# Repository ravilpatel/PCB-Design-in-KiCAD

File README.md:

# PCB Design

**Software:** KiCAD 9.0

## Table of Content

- [STM32 - UART, I2C and SWD (From Tutorial)](#stm32---uart-i2c-and-swd-from-tutorial)
- [Motion Detector using NE555 Timer IC](#motion-detector-using-ne555-timer-ic)

---

## STM32 - UART, I2C and SWD (From Tutorial)

Compact 2-layer STM32-based PCB

[Tutorial Video Link- Phill's Lab YT](https://www.youtube.com/watch?v=aVUqaB0IMh4&pp=ygULS0lDQUQgU3RtMzI%3D)

<div align="center">

</div>

### Design specifications

* **Microcontroller (MCU):** STM32F103C8T6
* **Layers:** 2 (Top / Bottom)
* **Board dimensions:** 41 mm × 28.8 mm
* **Substrate:** FR4, 1.6 mm thickness
* **Files included:** KiCAD project files, schematic, PCB layout, Gerber export instructions, BOM
* **Protocols supported:** UART, I2C, SWD

**[Project Repo](/STM32-I2C_UART_SWD)**

---

## Motion Detector using NE555 Timer IC

2-Layer NE555 Timer IC with IR Sensor 

<div align="center">

</div>

### Design specifications

* **Integrated Circuit (IC):** NE555 Timer IC
* **Layers:** 2 (Top / Bottom)
* **Board dimensions:** 65.0 mm × 32.4 mm
* **Substrate:** FR4, 1.6 mm thickness
* **Files included:** KiCAD project files, schematic, PCB layout, Gerber export instructions, BOM

**[Project Repo](/MotionDetector_555Timer)**

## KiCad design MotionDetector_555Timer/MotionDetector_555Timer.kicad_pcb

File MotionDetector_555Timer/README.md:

# NE555 Timer IC based PCB — KiCAD 9.0

**2-layer Motion Detector using NE555**

This repository contains the KiCAD 9.0 project files, documentation and assets for a compact 2-layer PCB built with NE555 Timer IC. The board is designed for manufacturability on standard FR4 (1.6 mm) and targets hobbyist / low-volume production.

<div align="center">

</div>

---

## Design specifications

* **Design software:** KiCAD 9.0
* **Integrated Circuit (IC):** NE555 Timer IC (schematic & part references in BOM)
* **Layers:** 2 (Top / Bottom)
* **Board dimensions:** **65.0 mm × 32.4 mm**
* **Substrate:** FR4, **1.6 mm** thickness
* **Files included:** KiCAD project files, schematic, PCB layout, Gerber export instructions, BOM
* **Protocols supported:** UART, I2C, SWD

---

## Repository layout

```
/ (repo root)
├─ README.md
├─ MotionDetector_555Timer.kicad_pcb
├─ MotionDetector_555Timer.kicad_sch
├─ MotionDetector_555Timer.kicad_pro
├─ MotionDetector_555Timer.kicad_prl              
├─ /Manufacturing/            # Generated Gerber + drill files (ready for fab) in zip, BOM in CSV
├─ /images/                   # Schematic + top/bottom/layers view images
│   ├─ schematic.png
|    ├─ PCB.png
│   ├─ top.png
│   ├─ bottom.png
│   └─ layers.png
```

---

## Schematic Sheet

---

## PCB View

**Top View**

**Bottom View**

**Layers View**

---

## BOM

Autogenerated BOM from KiCAD
| Reference   | Qty | Value                | DNP | Exclude from BOM  | Footprint                                                                      | Datasheet                                                        |
| ----------- | --- | -------------------- | --- | ----------------- | ------------------------------------------------------------------------------ | ---------------------------------------------------------------- |
| C1          | 1   | 1u                   |     |                   | Capacitor_SMD:C_0201_0603Metric                                                | ~                                                                |
| D1,D3       | 2   | 1N4148WT             |     |                   | Diode_SMD:D_SOD-523                                                            | https://www.diodes.com/assets/Datasheets/ds30396.pdf             |
| D2          | 1   | LED                  |     |                   | LED_SMD:LED_0201_0603Metric                                                    | ~                                                                |
| H1,H2,H3,H4 | 4   | MountingHole         |     | Excluded from BOM | MountingHole:MountingHole_2.1mm                                                | ~                                                                |
| J1          | 1   | Screw_Terminal_01x02 |     |                   | TerminalBlock_Phoenix:TerminalBlock_Phoenix_MKDS-1,5-2_1x02_P5.00mm_Horizontal | ~                                                                |
| J2          | 1   | Jack-DC              |     |                   | Connector_BarrelJack:BarrelJack_Horizontal                                     | ~                                                                |
| K1,K2       | 2   | FINDER-36.11         |     |                   | Relay_THT:Relay_SPDT_Finder_36.11                                              | https://gfinder.findernet.com/public/attachments/36/EN/S36EN.pdf |
| Q1          | 1   | BC557                |     |                   | Package_TO_SOT_THT:TO-92_Inline                                                | https://www.onsemi.com/pub/Collateral/BC556BTA-D.pdf             |
| Q2          | 1   | BC547                |     |                   | Package_TO_SOT_THT:TO-92_Inline                                                | https://www.onsemi.com/pub/Collateral/BC550-D.pdf                |
| R1          | 1   | 100k                 |     |                   | Resistor_SMD:R_0201_0603Metric                                                 | ~                                                                |
| R2,R3,R4    | 3   | 220k                 |     |                   | Resistor_SMD:R_0201_0603Metric                                                 | ~                                                                |
| R5          | 1   | 1k                   |     |                   | Resistor_SMD:R_01005_0402Metric                                                | ~                                                                |
| R6          | 1   | 240k                 |     |                   | Resistor_SMD:R_0201_0603Metric                                                 | ~                                                                |
| R7,R8       | 2   | 220                  |     |                   | Resistor_SMD:R_01005_0402Metric                                                | ~                                                                |
| U1          | 1   | NE555D               |     |                   | Package_SO:SOIC-8_3.9x4.9mm_P1.27mm                                            | http://www.ti.com/lit/ds/symlink/ne555.pdf                       |
| U2          | 1   | TSSP58038            |     |                   | OptoDevice:Vishay_MINICAST-3Pin                                                | http://www.vishay.com/docs/82476/tssp58p38.pdf                   |

---

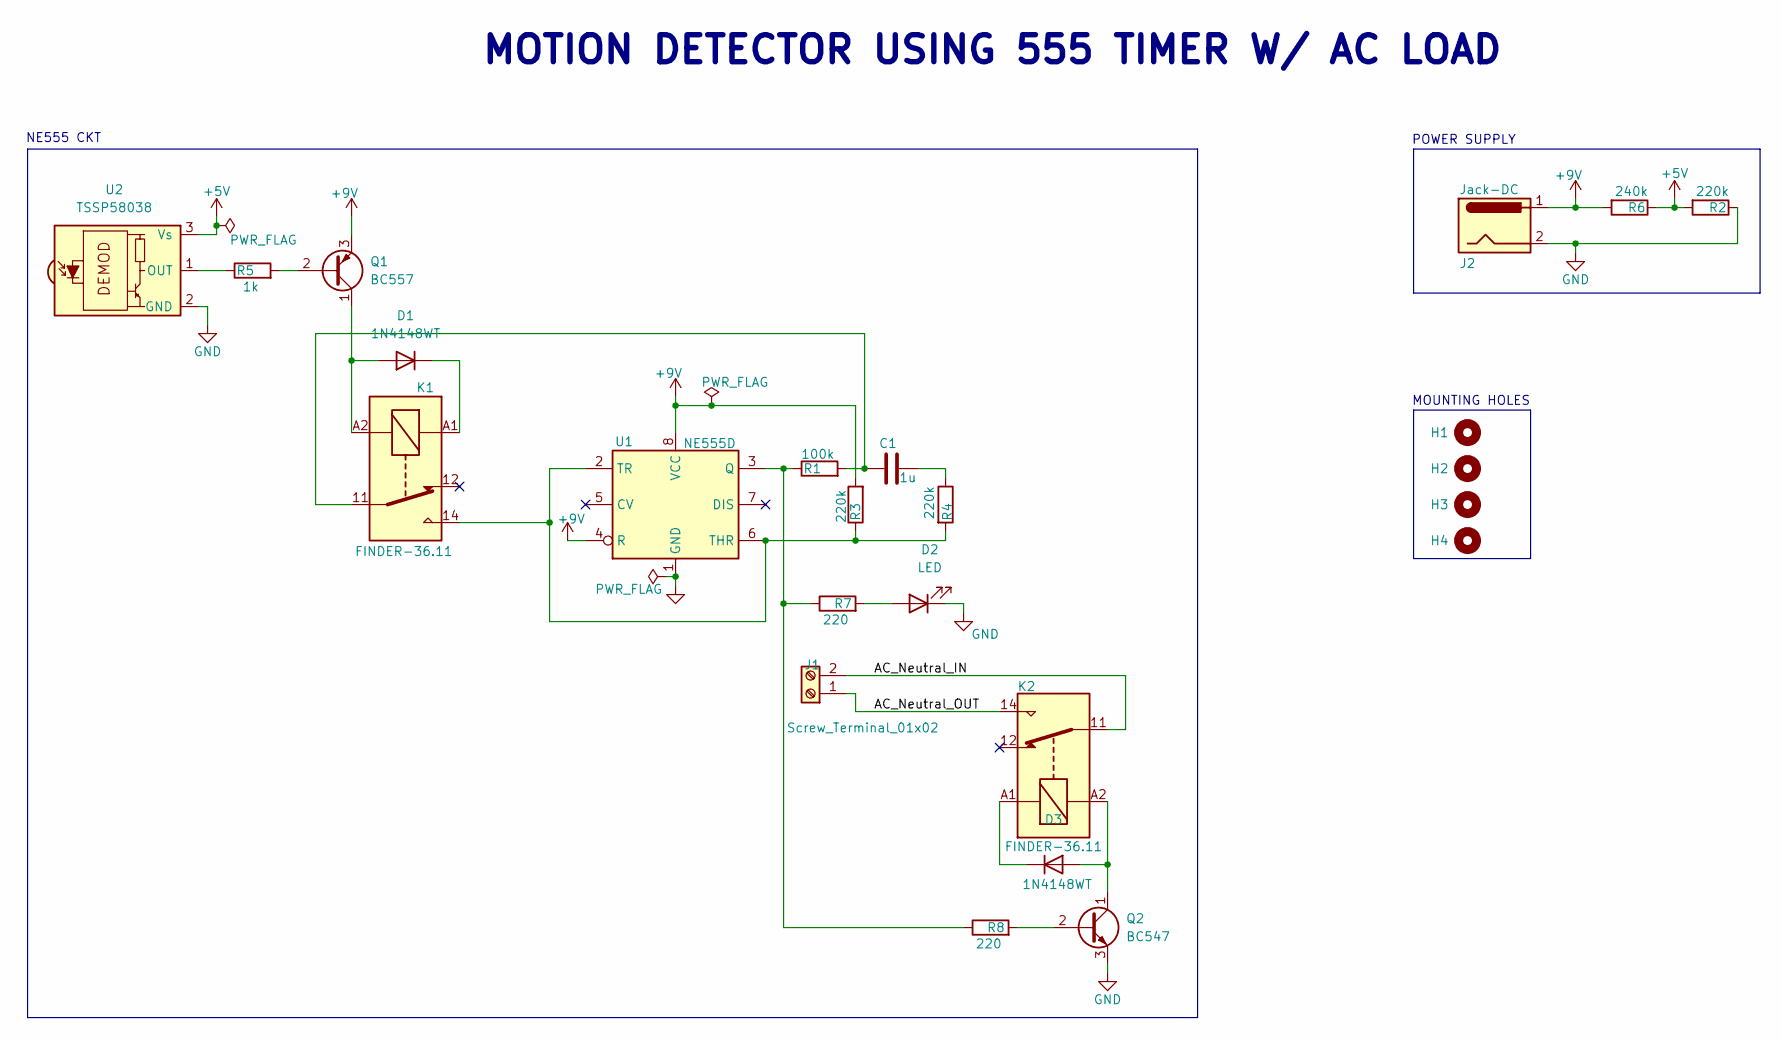
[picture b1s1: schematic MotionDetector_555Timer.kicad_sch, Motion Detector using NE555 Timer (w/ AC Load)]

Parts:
C1: 1u; C_0201_0603Metric
D1, D3: 1N4148WT; D_SOD-523
D2: LED; LED_0201_0603Metric
H1, H2, H3, H4: MountingHole; MountingHole_2.1mm
J1: Screw_Terminal_01x02; TerminalBlock_Phoenix_MKDS-1,5-2_1x02_P5.00mm_Horizontal
J2: Jack-DC; BarrelJack_Horizontal
K1, K2: FINDER-36.11; Relay_SPDT_Finder_36.11
Q1: BC557; TO-92_Inline
Q2: BC547; TO-92_Inline
R1: 100k; R_0201_0603Metric
R2, R3, R4: 220k; R_0201_0603Metric
R5: 1k; R_01005_0402Metric
R6: 240k; R_0201_0603Metric
R7, R8: 220; R_01005_0402Metric
U1: NE555D; SOIC-8_3.9x4.9mm_P1.27mm
U2: TSSP58038; Vishay_MINICAST-3Pin

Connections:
+5V: R2.2, R6.1, U2.3 (Vs)
+9V: J2.1, Q1.3 (E), R3.2, R6.2, U1.4 (R), U1.8 (VCC); also elsewhere on the board
/AC_Neutral_IN: J1.2, K2.11
/AC_Neutral_OUT: J1.1, K2.14
GND: D2.1 (K), J2.2, Q2.3 (E), R2.1, U1.1 (GND), U2.2 (GND); also elsewhere on the board
unnamed: C1.1, K1.11, R1.2
unnamed: C1.2, R4.1
unnamed: D1.2 (A), K1.A2, Q1.1 (C)
unnamed: D1.1 (K), K1.A1
unnamed 9: D2.2 (A), R7.2; also elsewhere on the board
unnamed: D3.2 (A), K2.A2, Q2.1 (C)
unnamed: D3.1 (K), K2.A1
unnamed: Q1.2 (B), R5.2
unnamed: Q2.2 (B), R8.2
unnamed 14: R1.1, R7.1, R8.1, U1.3 (Q); also elsewhere on the board
unnamed 15: K1.14, R3.1, R4.2, U1.2 (TR), U1.6 (THR); also elsewhere on the board
unnamed: R5.1, U2.1 (OUT)

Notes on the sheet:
MOTION DETECTOR USING 555 TIMER W/ AC LOAD
POWER SUPPLY
NE555 CKT
MOUNTING HOLES

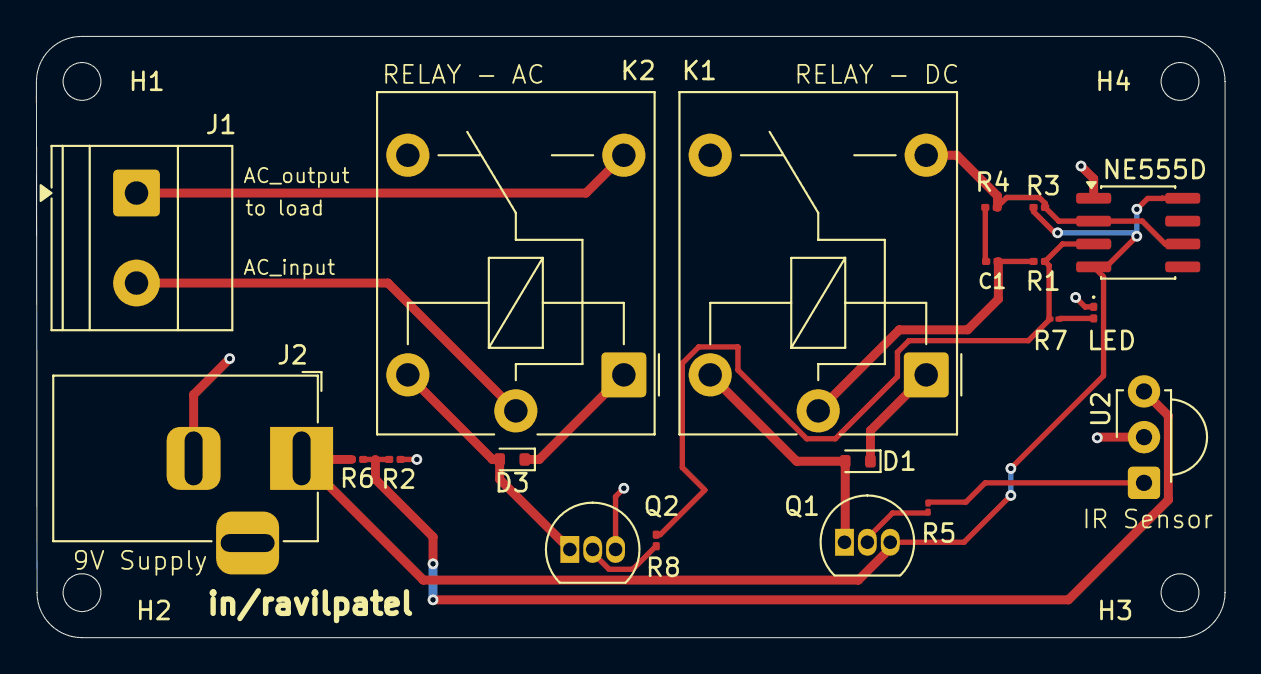
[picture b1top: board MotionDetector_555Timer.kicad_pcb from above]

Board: 2 copper layers, 66.0 x 33.4 mm, 24 parts (0 on the bottom side), 17 nets.

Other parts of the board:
LED: LED; LED_0201_0603Metric
NE555D: NE555D; SOIC-8_3.9x4.9mm_P1.27mm

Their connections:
+9V: NE555D.4 (R), NE555D.8 (VCC); also elsewhere on the board
GND: LED.1 (K), NE555D.1 (GND); also elsewhere on the board
unnamed 9: LED.2 (A); also elsewhere on the board
unnamed 14: NE555D.3 (Q); also elsewhere on the board
unnamed 15: NE555D.2 (TR), NE555D.6 (THR); also elsewhere on the board

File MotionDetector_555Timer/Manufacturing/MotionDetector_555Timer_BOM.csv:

Reference,Qty,Value,DNP,Exclude from BOM,Footprint,Datasheet
C1,1,1u,,,Capacitor_SMD:C_0201_0603Metric,~
"D1,D3",2,1N4148WT,,,Diode_SMD:D_SOD-523,https://www.diodes.com/assets/Datasheets/ds30396.pdf
D2,1,LED,,,LED_SMD:LED_0201_0603Metric,~
"H1,H2,H3,H4",4,MountingHole,,Excluded from BOM,MountingHole:MountingHole_2.1mm,~
J1,1,Screw_Terminal_01x02,,,"TerminalBlock_Phoenix:TerminalBlock_Phoenix_MKDS-1,5-2_1x02_P5.00mm_Horizontal",~
J2,1,Jack-DC,,,Connector_BarrelJack:BarrelJack_Horizontal,~
"K1,K2",2,FINDER-36.11,,,Relay_THT:Relay_SPDT_Finder_36.11,https://gfinder.findernet.com/public/attachments/36/EN/S36EN.pdf
Q1,1,BC557,,,Package_TO_SOT_THT:TO-92_Inline,https://www.onsemi.com/pub/Collateral/BC556BTA-D.pdf
Q2,1,BC547,,,Package_TO_SOT_THT:TO-92_Inline,https://www.onsemi.com/pub/Collateral/BC550-D.pdf
R1,1,100k,,,Resistor_SMD:R_0201_0603Metric,~
"R2,R3,R4",3,220k,,,Resistor_SMD:R_0201_0603Metric,~
R5,1,1k,,,Resistor_SMD:R_01005_0402Metric,~
R6,1,240k,,,Resistor_SMD:R_0201_0603Metric,~
"R7,R8",2,220,,,Resistor_SMD:R_01005_0402Metric,~
U1,1,NE555D,,,Package_SO:SOIC-8_3.9x4.9mm_P1.27mm,http://www.ti.com/lit/ds/symlink/ne555.pdf
U2,1,TSSP58038,,,OptoDevice:Vishay_MINICAST-3Pin,http://www.vishay.com/docs/82476/tssp58p38.pdf

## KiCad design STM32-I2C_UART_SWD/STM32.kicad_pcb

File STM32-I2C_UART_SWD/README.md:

# STM32 PCB — KiCAD 9.0

**Compact 2-layer STM32-based PCB**

This repository contains the KiCAD 9.0 project files, documentation and assets for a compact 2-layer PCB built around an STM32 microcontroller. The board is designed for manufacturability on standard FR4 (1.6 mm) and targets hobbyist / low-volume production.

**Resource**

[KiCad 6 STM32 PCB Design Full Tutorial - Phil's Lab](https://www.youtube.com/watch?v=aVUqaB0IMh4&pp=ygULS0lDQUQgU3RtMzI%3D)

---

## Design specifications

* **Design software:** KiCAD 9.0
* **Microcontroller (MCU):** STM32 (schematic & part references in BOM)
* **Layers:** 2 (Top / Bottom)
* **Board dimensions:** **41 mm × 28.8 mm**
* **Substrate:** FR4, **1.6 mm** thickness
* **Files included:** KiCAD project files, schematic, PCB layout, Gerber export instructions, BOM
* **Protocols supported:** UART, I2C, SWD

---

## Repository layout

```
/ (repo root)
├─ README.md
├─ STM32.kicad_pcb
├─ STM32.kicad_sch
├─ STM32.kicad_pro
├─ STM32.kicad_prl              
├─ /Manufacturing/            # Generated Gerber + drill files (ready for fab) in zip, BOM in CSV
├─ /images/                   # Schematic + top/bottom/layers view images
│   ├─ schematic.png
│   ├─ top_view.png
│   ├─ bottom_view.png
│   └─ layers_view.png
```

---

## Schematic Sheet

---

## PCB View

**Top View**

**Bottom View**

**Layers View**

---

## BOM

Autogenerated BOM from KiCAD

| Reference       | Qty | Value          | Footprint                                                  | Datasheet                                                |
| --------------- | --- | -------------- | ---------------------------------------------------------- | -------------------------------------------------------- |
| C1              | 1   | 10u            | Capacitor_SMD:C_0603_1608Metric                            | ~                                                        |
| C2,C3,C4,C5,C11 | 5   | 100n           | Capacitor_SMD:C_0402_1005Metric                            | ~                                                        |
| C6              | 1   | 10n            | Capacitor_SMD:C_0402_1005Metric                            | ~                                                        |
| C7,C8           | 2   | 1u             | Capacitor_SMD:C_0402_1005Metric                            | ~                                                        |
| C9,C10          | 2   | 22u            | Capacitor_SMD:C_0805_2012Metric                            | ~                                                        |
| C12,C13         | 2   | 10p            | Capacitor_SMD:C_0402_1005Metric                            | ~                                                        |
| D1              | 1   | RED            | LED_SMD:LED_0603_1608Metric                                | ~                                                        |
| FB1             | 1   | 120R           | Inductor_SMD:L_0603_1608Metric                             | ~                                                        |
| H1,H2,H3,H4     | 4   | MountingHole   | MountingHole:MountingHole_2.1mm                            | ~                                                        |
| J1              | 1   | USB_B_Micro    | Connector_USB:USB_Micro-B_Molex_47346-0001                 | ~                                                        |
| J2,J3,J4        | 3   | Conn_01x04_Pin | Connector_PinHeader_2.54mm:PinHeader_1x04_P2.54mm_Vertical | ~                                                        |
| R1              | 1   | 1K5            | Resistor_SMD:R_0402_1005Metric                             | ~                                                        |
| R2              | 1   | 10k            | Resistor_SMD:R_0402_1005Metric                             | ~                                                        |
| R3,R4,R5        | 3   | 1k5            | Resistor_SMD:R_0402_1005Metric                             | ~                                                        |
| SW1             | 1   | SW_SPDT        | Button_Switch_SMD:SW_SPDT_PCM12                            | ~                                                        |
| REG_3.3V        | 1   | AMS1117-3.3    | Package_TO_SOT_SMD:SOT-223-3_TabPin2                       | http://www.advanced-monolithic.com/pdf/ds1117.pdf        |
| MCU             | 1   | STM32F103C8T6  | Package_QFP:LQFP-48_7x7mm_P0.5mm                           | https://www.st.com/resource/en/datasheet/stm32f103c8.pdf |
| Y1              | 1   | 16MHz          | Crystal:Crystal_SMD_3225-4Pin_3.2x2.5mm                    | ~                                                        |

---

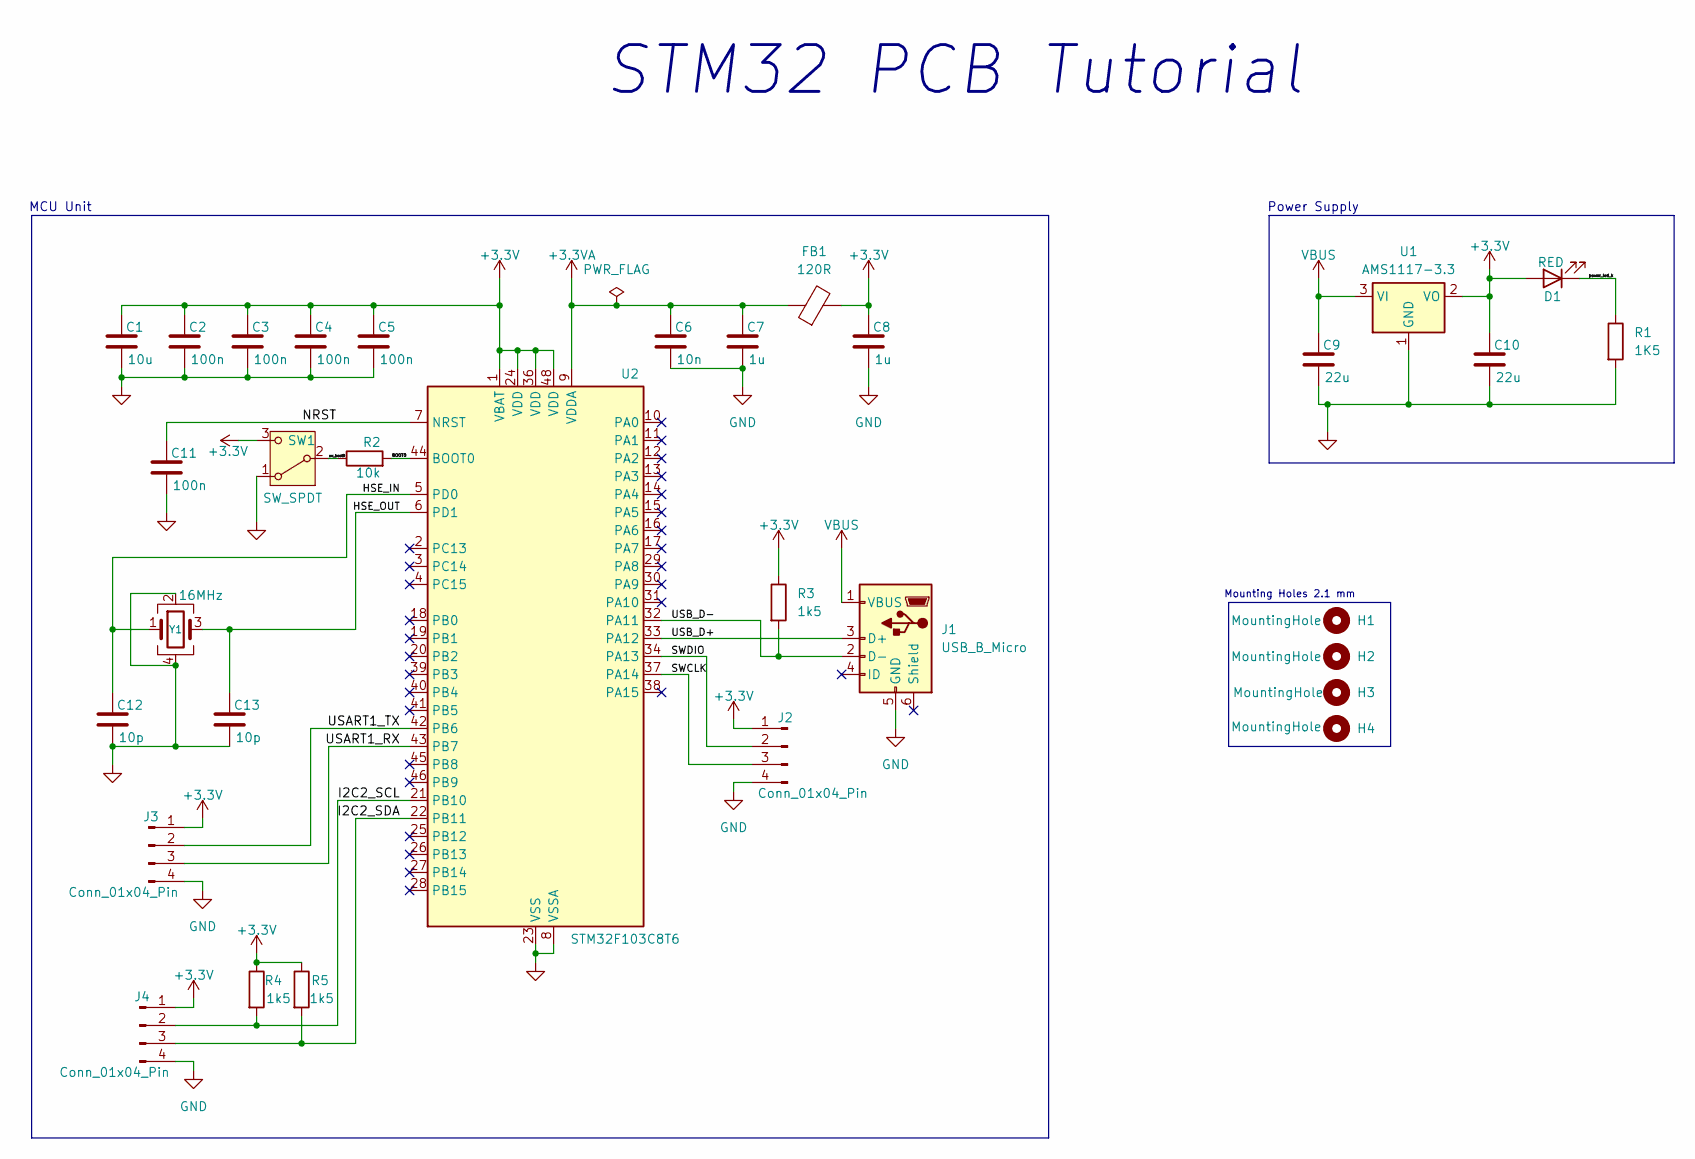
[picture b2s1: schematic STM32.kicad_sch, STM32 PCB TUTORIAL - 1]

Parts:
C1: 10u; C_0603_1608Metric
C2, C3, C4, C5, C11: 100n; C_0402_1005Metric
C6: 10n; C_0402_1005Metric
C7, C8: 1u; C_0402_1005Metric
C9, C10: 22u; C_0805_2012Metric
C12, C13: 10p; C_0402_1005Metric
D1: RED; LED_0603_1608Metric
FB1: 120R; L_0603_1608Metric
H1, H2, H3, H4: MountingHole; MountingHole_2.1mm
J1: USB_B_Micro; USB_Micro-B_Molex_47346-0001
J2, J3, J4: Conn_01x04_Pin; PinHeader_1x04_P2.54mm_Vertical
R1: 1K5; R_0402_1005Metric
R2: 10k; R_0402_1005Metric
R3, R4, R5: 1k5; R_0402_1005Metric
SW1: SW_SPDT; SW_SPDT_PCM12
U1: AMS1117-3.3; SOT-223-3_TabPin2
U2: STM32F103C8T6; LQFP-48_7x7mm_P0.5mm
Y1: 16MHz; Crystal_SMD_3225-4Pin_3.2x2.5mm

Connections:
+3.3V: C1.1, C2.1, C3.1, C4.1, C5.1, C8.1, C10.1, D1.2 (A), FB1.2, J2.1, J3.1, J4.1, R3.1, R4.1, R5.1, SW1.3 (C), U1.2 (VO), U2.1 (VBAT), U2.24 (VDD), U2.36 (VDD), U2.48 (VDD)
+3.3VA: C6.1, C7.1, FB1.1, U2.9 (VDDA)
/BOOT0: R2.2, U2.44 (BOOT0)
/HSE_IN: C12.1, U2.5 (PD0), Y1.1
/HSE_OUT: C13.1, U2.6 (PD1), Y1.3
/I2C2_SCL: J4.2, R4.2, U2.21 (PB10)
/I2C2_SDA: J4.3, R5.2, U2.22 (PB11)
/NRST: C11.1, U2.7 (NRST)
/SWCLK: J2.3, U2.37 (PA14)
/SWDIO: J2.2, U2.34 (PA13)
/USART1_RX: J3.3, U2.43 (PB7)
/USART1_TX: J3.2, U2.42 (PB6)
/USB_D+: J1.3 (D+), U2.33 (PA12)
/USB_D-: J1.2 (D-), R3.2, U2.32 (PA11)
/power_led_k: D1.1 (K), R1.1
/sw_boot0: R2.1, SW1.2 (B)
GND: C1.2, C2.2, C3.2, C4.2, C5.2, C6.2, C7.2, C8.2, C9.2, C10.2, C11.2, C12.2, C13.2, J1.5 (GND), J2.4, J3.4, J4.4, R1.2, SW1.1 (A), U1.1 (GND), U2.8 (VSSA), U2.23 (VSS), U2.35 (VSS), U2.47 (VSS), Y1.2, Y1.4
VBUS: C9.1, J1.1 (VBUS), U1.3 (VI)

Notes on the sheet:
MCU Unit
Mounting Holes 2.1 mm
STM32 PCB Tutorial
Power Supply

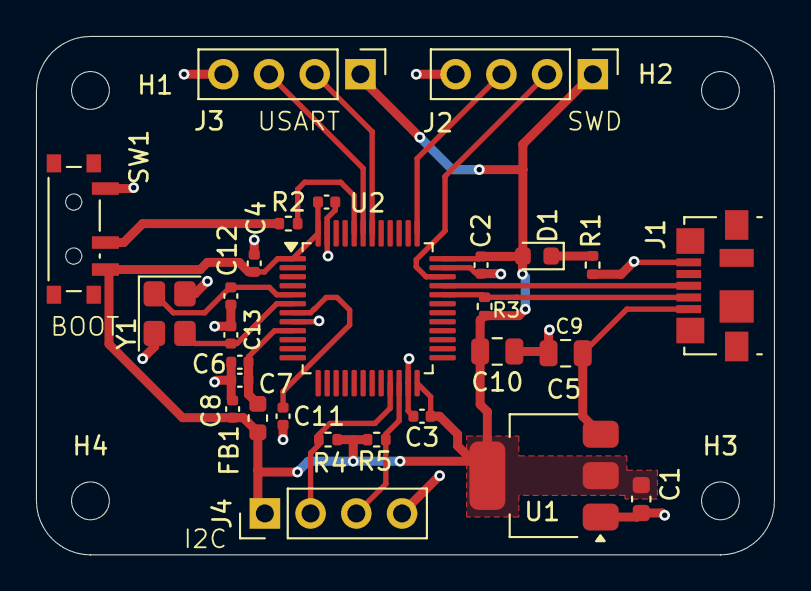
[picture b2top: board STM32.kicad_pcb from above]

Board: 2 copper layers, 41.0 x 28.8 mm, 32 parts (0 on the bottom side), 18 nets.

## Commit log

2025-11-25 Create STM32-I2C_UART_SWD
2025-11-25 STM32 Design Files and GBR Export files
2025-11-25 Create image folder
2025-11-25 images
2025-12-12 MotionDetector_555Timer
2025-12-12 Create CNAME
